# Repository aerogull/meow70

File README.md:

# Meow70

## Building the Board
My idea started with how I wanted a split keyboard that wasn't ortholinear or ergo. So, I took a picture of my Keychron K6 Pro, and designed a split keyboard off of it. It runs on 2 Raspberry Pi Picos (or drop in replacements) with a simple, open case design and qmk firmware.\
This was a pretty difficult build, I ended up redoing the routing and placement several times, going from a staggered edge with the controllers mounted underneath, to what I have today. The most difficult part was doing the render of the keyboard (which is still a WIP, this is just temporary). My KICAD always gave me destroyed meshes that would take hours to import into any software. Once I finally got something imported, it took me 2 days of constantly doing little things and saving my work before blender crashed. The final render took over 8 minutes to finish, so it was quite an undertaking getting it to work.

## Bill of Materials
* 1x set of pcbs
* 2x Raspberry Pi Pico H
* 69x Kailh Hotswap Sockets (MX Style)
* 69x 1N4148 Diodes
* 69x MX-Style Switches
* 4x Plate-Mounted Stabilizers
* 2x 0.91" I2C PCB-Mounted OLED Displays
* 2x TRRS Audio Jack Connectors
* 8x M3 Screws
* 8x M3 Heatset Inserts

## More Photos

## KICAD BOM (with prices for what I used)
|Quantity|Item|Designation|Price Each|Total Price + Shipping|Link|
|----|----|----|----|----|----|
|69|"MX-Hotswap"|"SW_Push"|$0.138|$9.65|[here](https://www.aliexpress.us/item/3256807039037559.html)|
|2|"RaspberryPi_Pico_Common_THT_wModel"|"RaspberryPi_Pico"|$4|Provided by HackClub HQ!||
|2|"SSD1306-0.91-OLED-4pin-128x32"|"~"|$1.845|$3.69|[here](https://www.aliexpress.us/item/3256805967573053.html)|
|2|"TENSILITY_54-00174" (PJ-332)|"AudioJack4"|$0.234|$2.34|[here](https://www.aliexpress.us/item/3256807580272301.html)|
|69|"D_DO-35_SOD27_P7.62mm_Horizontal"|"1N4148"|$0.0174|$1.74|[here](https://www.aliexpress.us/item/3256806058794623.html)|
|69|MX Mechanical Switches|Gateron G Pro 3.0 Silvers|$0.345|$50.11|[here](https://www.gateron.co/products/gateron-g-pro-3-0-switch-set?variant=40479583043673)
|69|Keycaps|3D Printed (Cherry or DSA)|Printing Legion||[this](https://github.com/rsheldiii/KeyV2) or [this](https://github.com/anhthang/dsa-keycap)|
|8|Heatset Inserts|97164A112|$0.0574|$5.74|[here](https://www.aliexpress.us/item/3256805603102147.html)|
|4|Stabilizers|Gateron 2u Stabs|$2.547|$15.28|[here](https://www.aliexpress.us/item/3256805212136654.html)|
|1|TRRS Cable|Random Aliexpress Coiled TRRS Cable|$6.94|$6.94|[here](https://www.aliexpress.us/item/3256806811164725.html)|
|1|Full Case|4 Parts Split Up for Printing|Self or Printing Legion||[here](https://github.com/aerogull/meow70/tree/main/prod)|
|8|Screws|3mm 0.5x16mm|$0.345|$2.76|[here](https://www.lowes.com/pd/Hillman-3mm-0-5-x-16mm-Allen-Drive-Cap-Screws-4-Count/50088880)|
|5|Sets of PCBs|JLCPCB|$20.70 (for 5)|$55.95|[here](https://cart.jlcpcb.com/quote?orderType=1&homeUploadNum=360e6b78f3044f3bb4ea106e3b9b02fb&businessType=example&fileName=keyboardv2_364.2375x100.5mm_for_Default.zip)|

[link to step model of completed board](https://hc-cdn.hel1.your-objectstorage.com/s/v3/b98df7d8c57167f14ca20340c5cecc1c217099e2_full_assembly_para.step)

## Completed Build!

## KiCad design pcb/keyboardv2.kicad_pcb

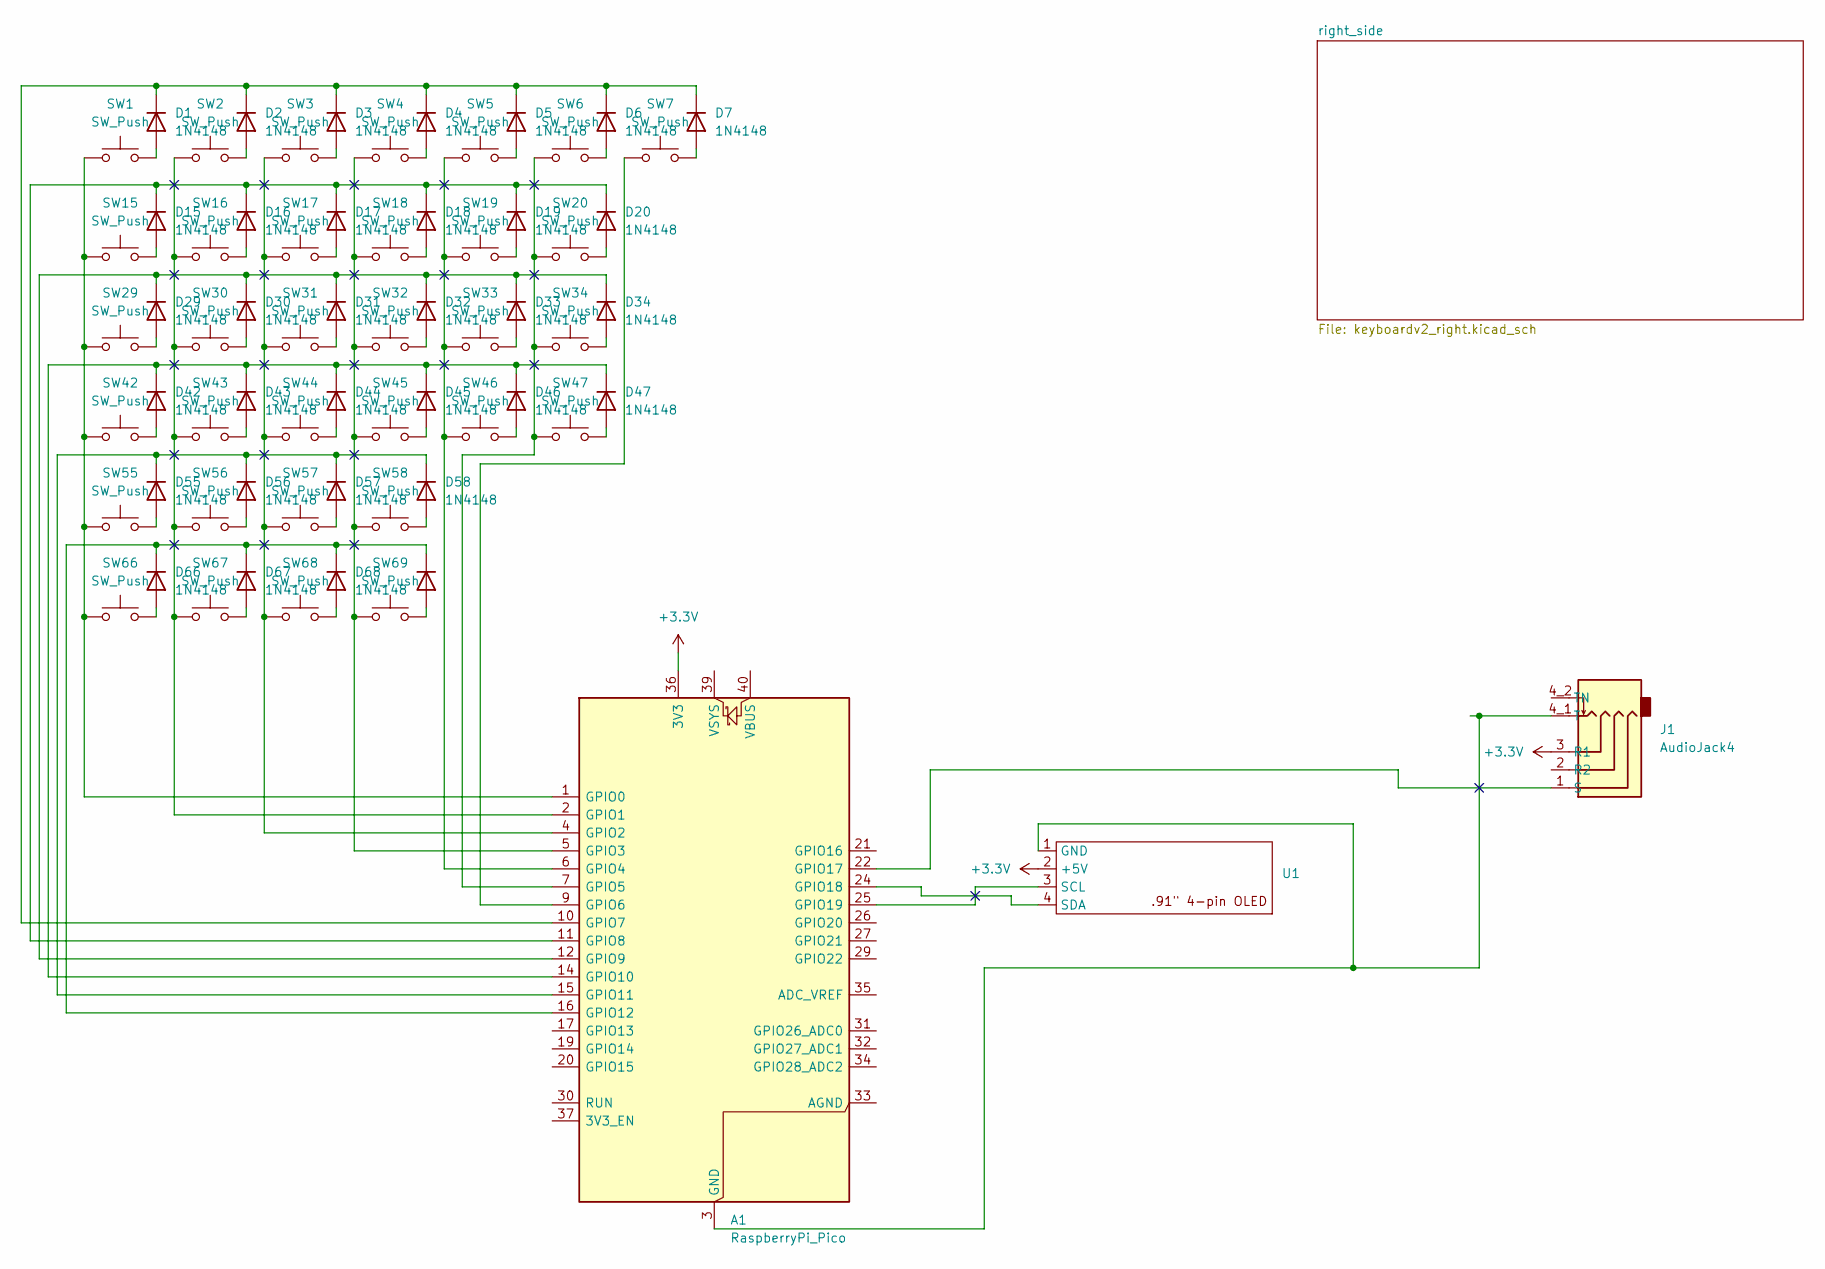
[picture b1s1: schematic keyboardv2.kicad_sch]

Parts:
A1: RaspberryPi_Pico; RaspberryPi_Pico_Common_THT
D1, D2, D3, D4, D5, D6, D7, D15, D16, D17, D18, D19, D20, D29, D30, D31, D32, D33, D34, D42, D43, D44, D45, D46, D47, D55, D56, D57, D58, D66, D67, D68, D69: 1N4148; D_DO-35_SOD27_P7.62mm_Horizontal
J1: AudioJack4; TENSILITY_54-00174
SW1, SW2, SW3, SW4, SW5, SW6, SW7, SW16, SW17, SW18, SW19, SW20, SW30, SW31, SW32, SW33, SW34, SW43, SW44, SW45, SW46, SW47, SW66, SW67, SW68, SW69: SW_Push; MX-Hotswap-1U
SW15: SW_Push; MX-Hotswap-1.25U
SW29, SW55, SW56, SW57: SW_Push; MX-Hotswap-1.5U
SW42: SW_Push; MX-Hotswap-1.75U
SW58: SW_Push; MX-Hotswap-2U
U1: SSD1306-0.91-OLED-4pin-128x32

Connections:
+3.3V: A1.36 (3V3), J1.3 (R1), U1.2 (+5V)
unnamed: A1.1 (GPIO0), SW1.1, SW15.1, SW29.1, SW42.1, SW55.1, SW66.1
unnamed: A1.2 (GPIO1), SW2.1, SW16.1, SW30.1, SW43.1, SW56.1, SW67.1
unnamed: A1.4 (GPIO2), SW3.1, SW17.1, SW31.1, SW44.1, SW57.1, SW68.1
unnamed: A1.5 (GPIO3), SW4.1, SW18.1, SW32.1, SW45.1, SW58.1, SW69.1
unnamed: A1.6 (GPIO4), SW5.1, SW19.1, SW33.1, SW46.1
unnamed: A1.7 (GPIO5), SW6.1, SW20.1, SW34.1, SW47.1
unnamed: A1.9 (GPIO6), SW7.1
unnamed: A1.10 (GPIO7), D1.1 (K), D2.1 (K), D3.1 (K), D4.1 (K), D5.1 (K), D6.1 (K), D7.1 (K)
unnamed: A1.11 (GPIO8), D15.1 (K), D16.1 (K), D17.1 (K), D18.1 (K), D19.1 (K), D20.1 (K)
unnamed: A1.12 (GPIO9), D29.1 (K), D30.1 (K), D31.1 (K), D32.1 (K), D33.1 (K), D34.1 (K)
unnamed: A1.14 (GPIO10), D42.1 (K), D43.1 (K), D44.1 (K), D45.1 (K), D46.1 (K), D47.1 (K)
unnamed: A1.15 (GPIO11), D55.1 (K), D56.1 (K), D57.1 (K), D58.1 (K)
unnamed: A1.16 (GPIO12), D66.1 (K), D67.1 (K), D68.1 (K), D69.1 (K)
unnamed: A1.22 (GPIO17), J1.1 (S)
unnamed: A1.24 (GPIO18), U1.4 (SDA)
unnamed: A1.25 (GPIO19), U1.3 (SCL)
unnamed: D1.2 (A), SW1.2
unnamed: D2.2 (A), SW2.2
unnamed: D3.2 (A), SW3.2
unnamed: D4.2 (A), SW4.2
unnamed: D5.2 (A), SW5.2
unnamed: D6.2 (A), SW6.2
unnamed: D7.2 (A), SW7.2
unnamed: D15.2 (A), SW15.2
unnamed: D16.2 (A), SW16.2
unnamed: D17.2 (A), SW17.2
unnamed: D18.2 (A), SW18.2
unnamed: D19.2 (A), SW19.2
unnamed: D20.2 (A), SW20.2
unnamed: D29.2 (A), SW29.2
unnamed: D30.2 (A), SW30.2
unnamed: D31.2 (A), SW31.2
unnamed: D32.2 (A), SW32.2
unnamed: D33.2 (A), SW33.2
unnamed: D34.2 (A), SW34.2
unnamed: D42.2 (A), SW42.2
unnamed: D43.2 (A), SW43.2
unnamed: D44.2 (A), SW44.2
unnamed: D45.2 (A), SW45.2
unnamed: D46.2 (A), SW46.2
unnamed: D47.2 (A), SW47.2
unnamed: D55.2 (A), SW55.2
unnamed: D56.2 (A), SW56.2
unnamed: D57.2 (A), SW57.2
unnamed: D58.2 (A), SW58.2
unnamed: D66.2 (A), SW66.2
unnamed: D67.2 (A), SW67.2
unnamed: D68.2 (A), SW68.2
unnamed: D69.2 (A), SW69.2
unnamed: A1.3 (GND), A1.8 (GND), A1.13 (GND), A1.18 (GND), A1.23 (GND), A1.28 (GND), A1.38 (GND), J1.4_1 (T), U1.1 (GND)

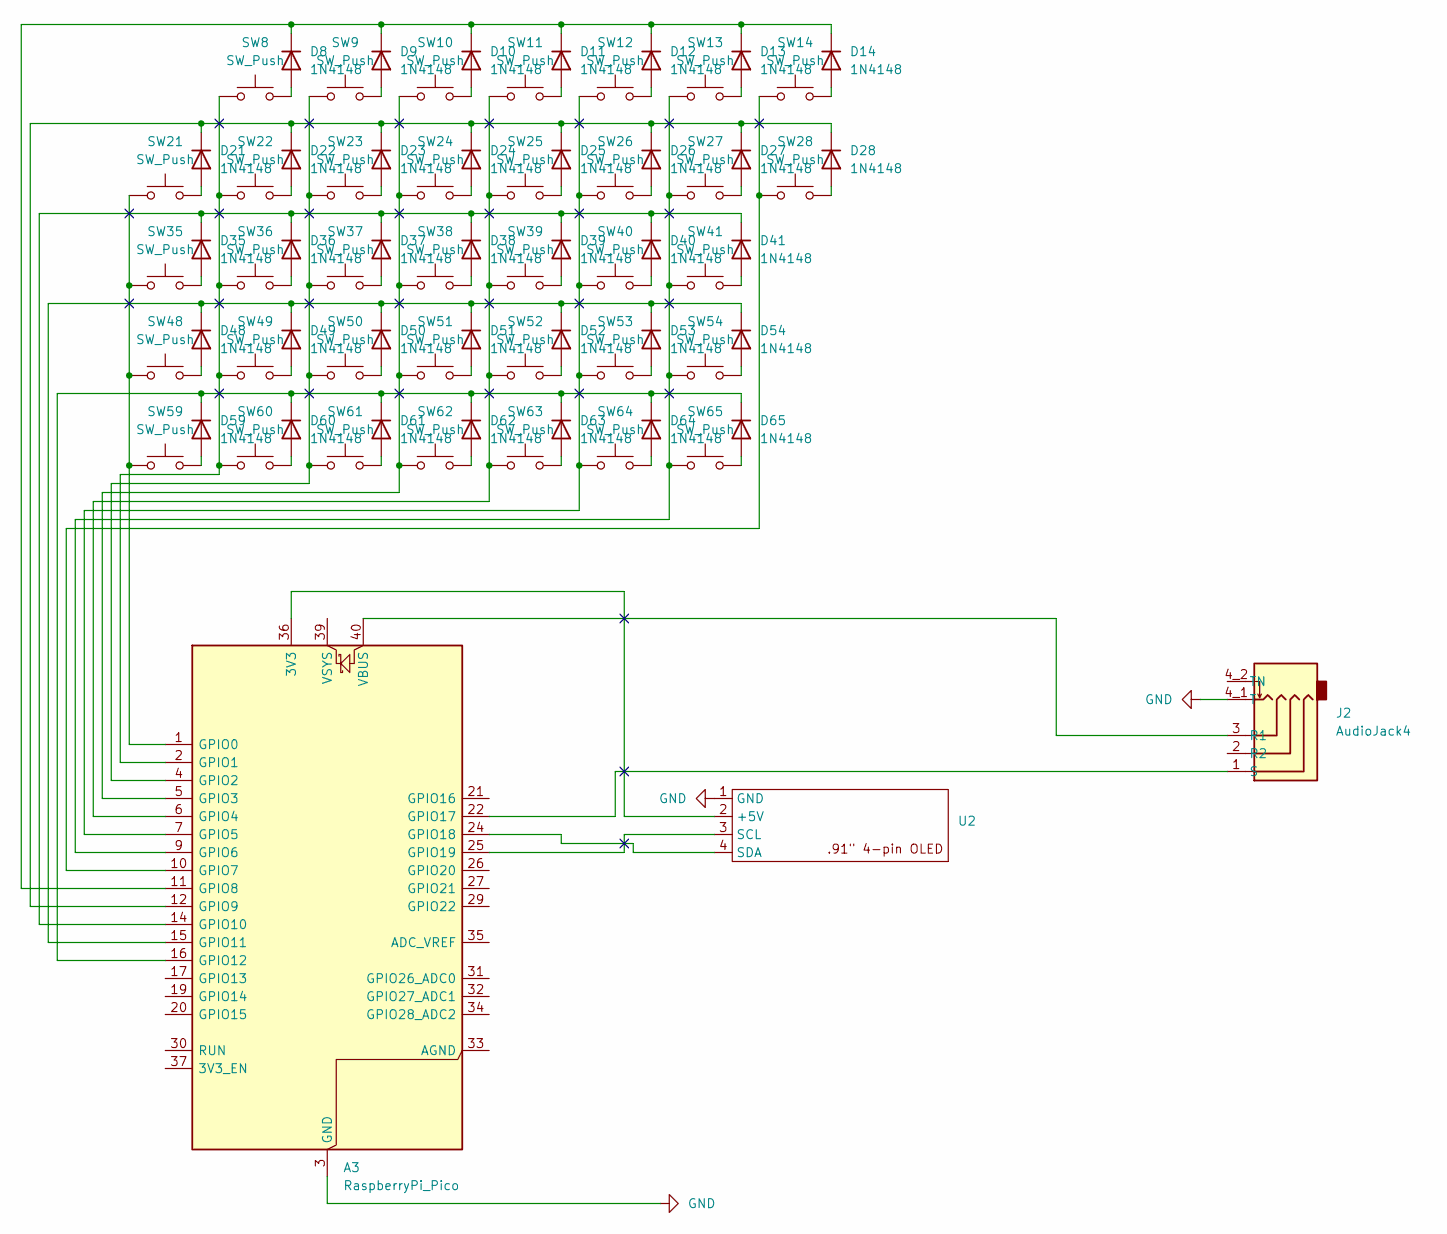
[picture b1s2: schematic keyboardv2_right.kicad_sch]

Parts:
A3: RaspberryPi_Pico; RaspberryPi_Pico_Common_THT
D8, D9, D10, D11, D12, D13, D14, D21, D22, D23, D24, D25, D26, D27, D28, D35, D36, D37, D38, D39, D40, D41, D48, D49, D50, D51, D52, D53, D54, D59, D60, D61, D62, D63, D64, D65: 1N4148; D_DO-35_SOD27_P7.62mm_Horizontal
J2: AudioJack4; TENSILITY_54-00174
SW8, SW9, SW10, SW11, SW12, SW13, SW21, SW22, SW23, SW24, SW25, SW26, SW27, SW28, SW35, SW36, SW37, SW38, SW39, SW40, SW48, SW49, SW50, SW51, SW52, SW54, SW60, SW61, SW62, SW63, SW64, SW65: SW_Push; MX-Hotswap-1U
SW14, SW41: SW_Push; MX-Hotswap-1.75U
SW53: SW_Push; MX-Hotswap-1.25U
SW59: SW_Push; MX-Hotswap-2U
U2: SSD1306-0.91-OLED-4pin-128x32

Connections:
GND: A3.3 (GND), A3.8 (GND), A3.13 (GND), A3.18 (GND), A3.23 (GND), A3.28 (GND), A3.38 (GND), J2.4_1 (T), U2.1 (GND)
unnamed: A3.36 (3V3), U2.2 (+5V)
unnamed: A3.1 (GPIO0), SW21.1, SW35.1, SW48.1, SW59.1
unnamed: A3.2 (GPIO1), SW8.1, SW22.1, SW36.1, SW49.1, SW60.1
unnamed: A3.4 (GPIO2), SW9.1, SW23.1, SW37.1, SW50.1, SW61.1
unnamed: A3.5 (GPIO3), SW10.1, SW24.1, SW38.1, SW51.1, SW62.1
unnamed: A3.6 (GPIO4), SW11.1, SW25.1, SW39.1, SW52.1, SW63.1
unnamed: A3.7 (GPIO5), SW12.1, SW26.1, SW40.1, SW53.1, SW64.1
unnamed: A3.9 (GPIO6), SW13.1, SW27.1, SW41.1, SW54.1, SW65.1
unnamed: A3.10 (GPIO7), SW14.1, SW28.1
unnamed: A3.11 (GPIO8), D8.1 (K), D9.1 (K), D10.1 (K), D11.1 (K), D12.1 (K), D13.1 (K), D14.1 (K)
unnamed: A3.12 (GPIO9), D21.1 (K), D22.1 (K), D23.1 (K), D24.1 (K), D25.1 (K), D26.1 (K), D27.1 (K), D28.1 (K)
unnamed: A3.14 (GPIO10), D35.1 (K), D36.1 (K), D37.1 (K), D38.1 (K), D39.1 (K), D40.1 (K), D41.1 (K)
unnamed: A3.15 (GPIO11), D48.1 (K), D49.1 (K), D50.1 (K), D51.1 (K), D52.1 (K), D53.1 (K), D54.1 (K)
unnamed: A3.16 (GPIO12), D59.1 (K), D60.1 (K), D61.1 (K), D62.1 (K), D63.1 (K), D64.1 (K), D65.1 (K)
unnamed: A3.22 (GPIO17), J2.1 (S)
unnamed: A3.24 (GPIO18), U2.4 (SDA)
unnamed: A3.25 (GPIO19), U2.3 (SCL)
unnamed: A3.40 (VBUS), J2.3 (R1)
unnamed: D8.2 (A), SW8.2
unnamed: D9.2 (A), SW9.2
unnamed: D10.2 (A), SW10.2
unnamed: D11.2 (A), SW11.2
unnamed: D12.2 (A), SW12.2
unnamed: D13.2 (A), SW13.2
unnamed: D14.2 (A), SW14.2
unnamed: D21.2 (A), SW21.2
unnamed: D22.2 (A), SW22.2
unnamed: D23.2 (A), SW23.2
unnamed: D24.2 (A), SW24.2
unnamed: D25.2 (A), SW25.2
unnamed: D26.2 (A), SW26.2
unnamed: D27.2 (A), SW27.2
unnamed: D28.2 (A), SW28.2
unnamed: D35.2 (A), SW35.2
unnamed: D36.2 (A), SW36.2
unnamed: D37.2 (A), SW37.2
unnamed: D38.2 (A), SW38.2
unnamed: D39.2 (A), SW39.2
unnamed: D40.2 (A), SW40.2
unnamed: D41.2 (A), SW41.2
unnamed: D48.2 (A), SW48.2
unnamed: D49.2 (A), SW49.2
unnamed: D50.2 (A), SW50.2
unnamed: D51.2 (A), SW51.2
unnamed: D52.2 (A), SW52.2
unnamed: D53.2 (A), SW53.2
unnamed: D54.2 (A), SW54.2
unnamed: D59.2 (A), SW59.2
unnamed: D60.2 (A), SW60.2
unnamed: D61.2 (A), SW61.2
unnamed: D62.2 (A), SW62.2
unnamed: D63.2 (A), SW63.2
unnamed: D64.2 (A), SW64.2
unnamed: D65.2 (A), SW65.2

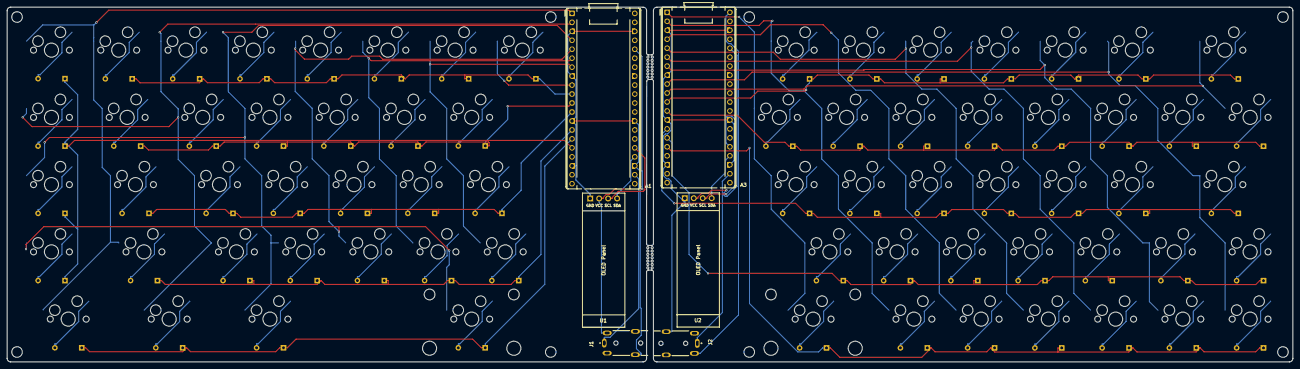
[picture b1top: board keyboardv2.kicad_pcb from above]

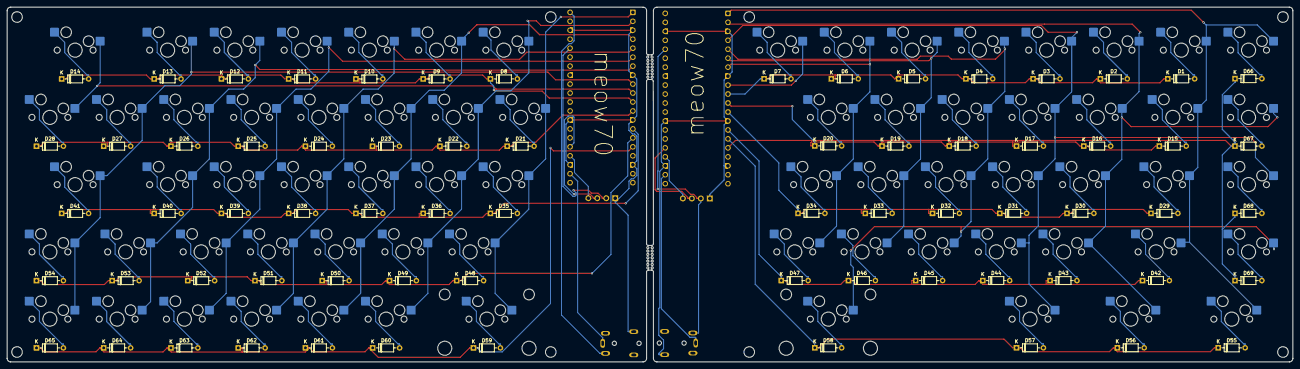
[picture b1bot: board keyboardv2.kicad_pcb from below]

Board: 2 copper layers, 364.2 x 100.5 mm, 144 parts (69 on the bottom side), 106 nets.

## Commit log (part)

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2025-02-13 init for testing
2025-03-09 finished v2 of keeb
2025-03-10 changed obj to step
2025-03-10 added pcb source
2025-04-02 Update readme.md to reflect recent changes
2025-04-02 Update keyboard.json to reflect recent changes
2025-10-06 minor updates with bom added
2025-10-06 minor bom updates
2025-10-06 minor bom updates v2
2025-10-06 minor bom updates v3
2025-10-06 oopsie, it borke
2025-10-07 bom changes and layout changes
2025-10-08 working on a full 3d model of the board
2025-10-09 take 3
2025-10-09 updated gerbers
2025-10-09 oopsie, forgor save
2025-10-09 updated bom with links and other goodies
2025-10-09 oopsie
2025-10-09 second oopsie
2025-10-13 updated bom to include pcb
2025-10-13 my git is very broken
2025-10-17 updated prices in bom
2025-10-18 bom changes
2025-10-18 updated bom v2
2025-11-08 old model
2025-11-10 added link to step
2026-06-29 firmware changes and via compatible
2026-06-29 README changes
